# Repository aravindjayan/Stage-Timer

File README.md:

# Stage-Timer
A custom stage timer made for TEDx FISAT. Uses 2.3" Seven segment displays to indicate time.

A PCB was designed only for the seven segment displays consisting of ULN2003 as the digit driver and BD140 transistor as digit drivers.
The display was driven with an Arduino Pro Mini.

The timer was programmed in Arduino and the following libraries were used.
* [Countimer](https://github.com/inflop/Countimer) by inflop
* [SevenSeg](https://github.com/sigvaldm/SevenSeg) by sigvaldm

Illustrator design is included for a Laser-Cut housing in 3mm acrylic.

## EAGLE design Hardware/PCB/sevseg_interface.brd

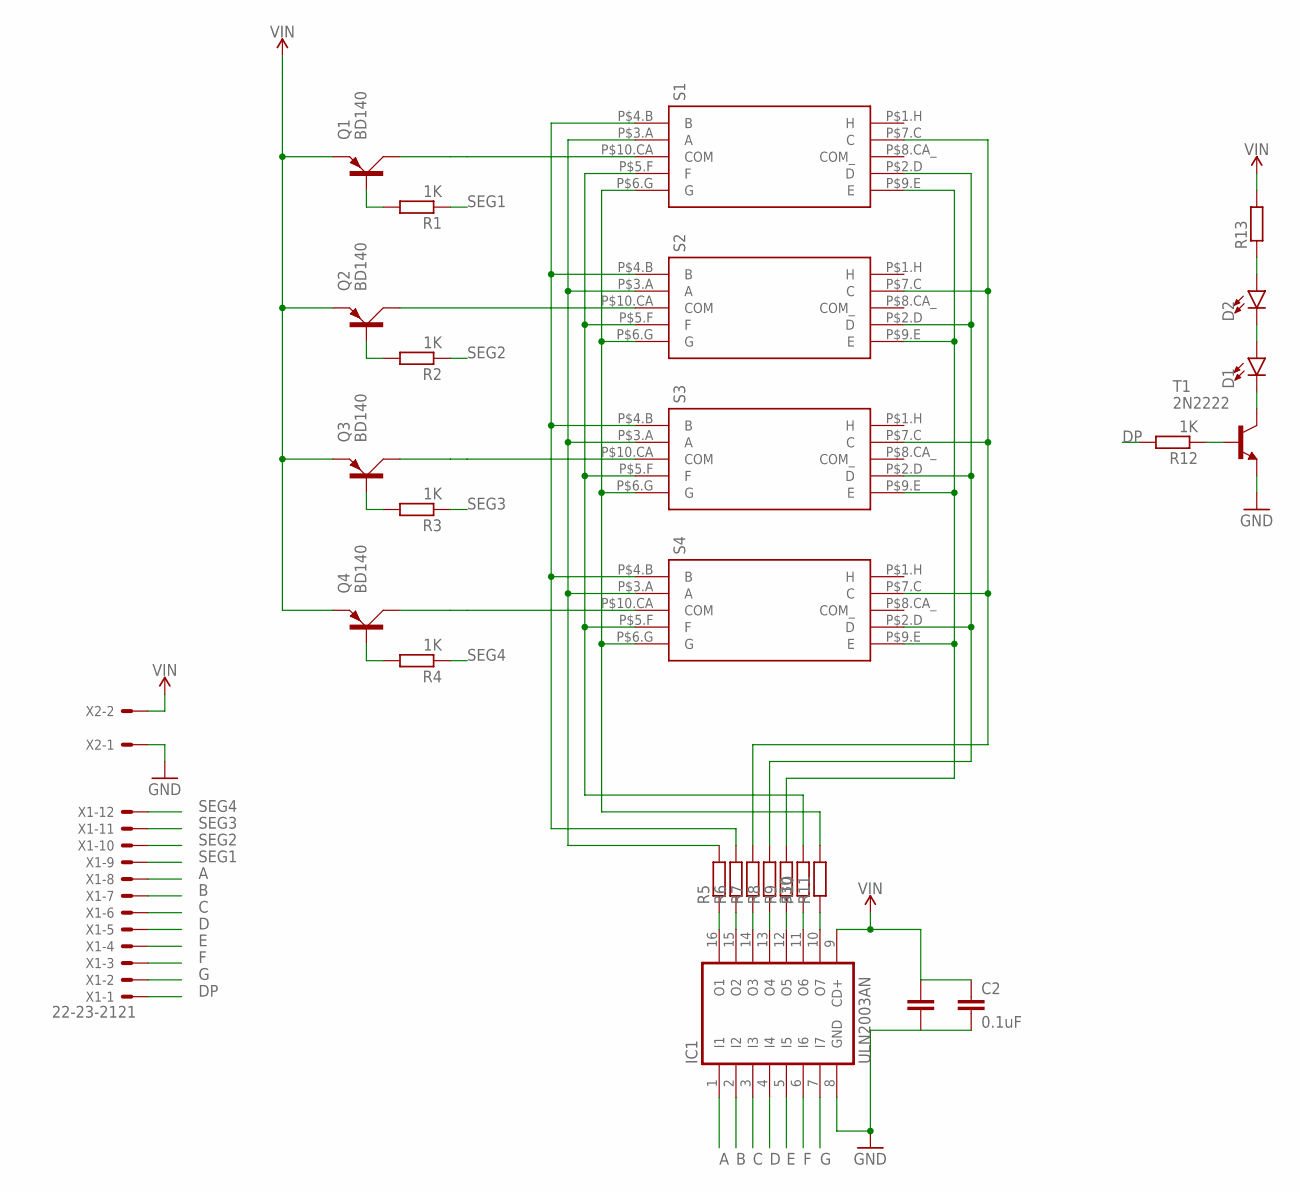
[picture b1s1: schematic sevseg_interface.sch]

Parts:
C2: 0.1uF; CAP-PTH-SMALL-KIT
D1, D2: LED5MM; LED_5MM
IC1: ULN2003AN; DIL16
Q1, Q2, Q3, Q4: BD140; TO126AV
R1, R2, R3, R4, R12: 1K; 0204/7
R5, R6, R7, R9, R10, R11, R13: R-EU_0204/7; 0204/7
R8: 330; 0204/7
S1, S2, S3, S4: 7SEG_2.3IN_70MM_CA; 2.3INCH_70MM
T1: 2N2222; TO18
X1: 22-23-2121
X2: KK-156-2

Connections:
A: IC1.1 (I1), X1.8
B: IC1.2 (I2), X1.7
C: IC1.3 (I3), X1.6
D: IC1.4 (I4), X1.5
DP: R12.2, X1.1
E: IC1.5 (I5), X1.4
F: IC1.6 (I6), X1.3
G: IC1.7 (I7), X1.2
GND: C2.2, IC1.8 (GND), T1.1 (E), X2.1
unnamed: R6.2, S1.P$4.B (B), S2.P$4.B (B), S3.P$4.B (B), S4.P$4.B (B)
unnamed: R5.2, S1.P$3.A (A), S2.P$3.A (A), S3.P$3.A (A), S4.P$3.A (A)
unnamed: Q1.C, S1.P$10.CA (COM)
unnamed: Q2.C, S2.P$10.CA (COM)
unnamed: Q3.C, S3.P$10.CA (COM)
unnamed: Q4.C, S4.P$10.CA (COM)
unnamed: R10.2, S1.P$5.F (F), S2.P$5.F (F), S3.P$5.F (F), S4.P$5.F (F)
unnamed: R11.2, S1.P$6.G (G), S2.P$6.G (G), S3.P$6.G (G), S4.P$6.G (G)
unnamed: R7.2, S1.P$7.C (C), S2.P$7.C (C), S3.P$7.C (C), S4.P$7.C (C)
unnamed: R8.2, S1.P$2.D (D), S2.P$2.D (D), S3.P$2.D (D), S4.P$2.D (D)
unnamed: R9.2, S1.P$9.E (E), S2.P$9.E (E), S3.P$9.E (E), S4.P$9.E (E)
unnamed: R12.1, T1.2 (B)
unnamed: Q2.B, R2.2
unnamed: Q3.B, R3.2
unnamed: Q4.B, R4.2
unnamed: Q1.B, R1.2
unnamed: IC1.16 (O1), R5.1
unnamed: IC1.15 (O2), R6.1
unnamed: IC1.14 (O3), R7.1
unnamed: IC1.13 (O4), R8.1
unnamed: IC1.12 (O5), R9.1
unnamed: IC1.11 (O6), R10.1
unnamed: IC1.10 (O7), R11.1
unnamed: D1.K (C), T1.3 (C)
unnamed: D1.A, D2.K (C)
unnamed: D2.A, R13.1
SEG1: R1.1, X1.9
SEG2: R2.1, X1.10
SEG3: R3.1, X1.11
SEG4: R4.1, X1.12
VIN: C2.1, IC1.9 (CD+), Q1.E, Q2.E, Q3.E, Q4.E, R13.2, X2.2

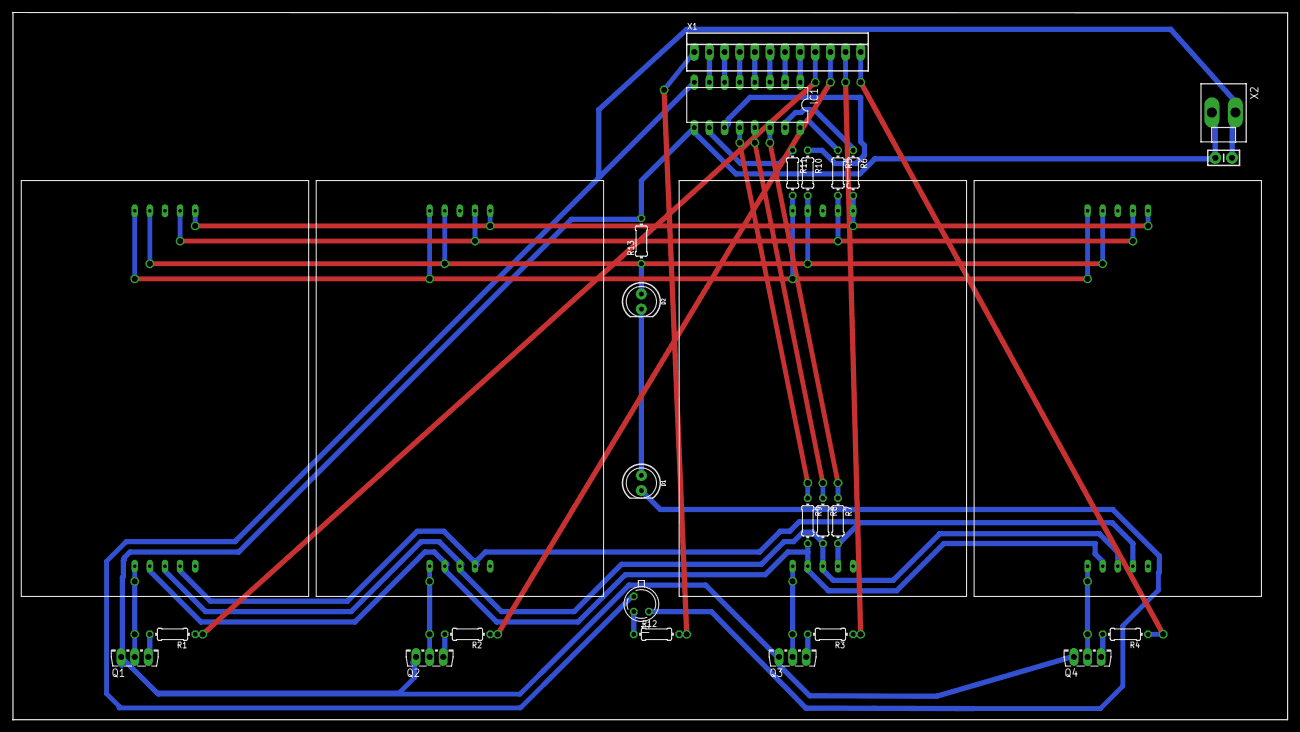
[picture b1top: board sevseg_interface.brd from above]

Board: 2 copper layers, 214.2 x 118.8 mm, 28 parts (0 on the bottom side), 40 nets.

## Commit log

2018-09-08 Initial Commit
    Added detailedREADME.
2018-09-08 Fixed broken links
2018-09-09 Added AutoCAD compatible dwg format file

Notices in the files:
parts and their libraries:
SparkFun-LED: Licensing: Creative Commons ShareAlike 4.0 International - https://creativecommons.org/licenses/by-sa/4.0
